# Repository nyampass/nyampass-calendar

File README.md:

# nyampass-calendar

A project to manage Calendar PCBs.

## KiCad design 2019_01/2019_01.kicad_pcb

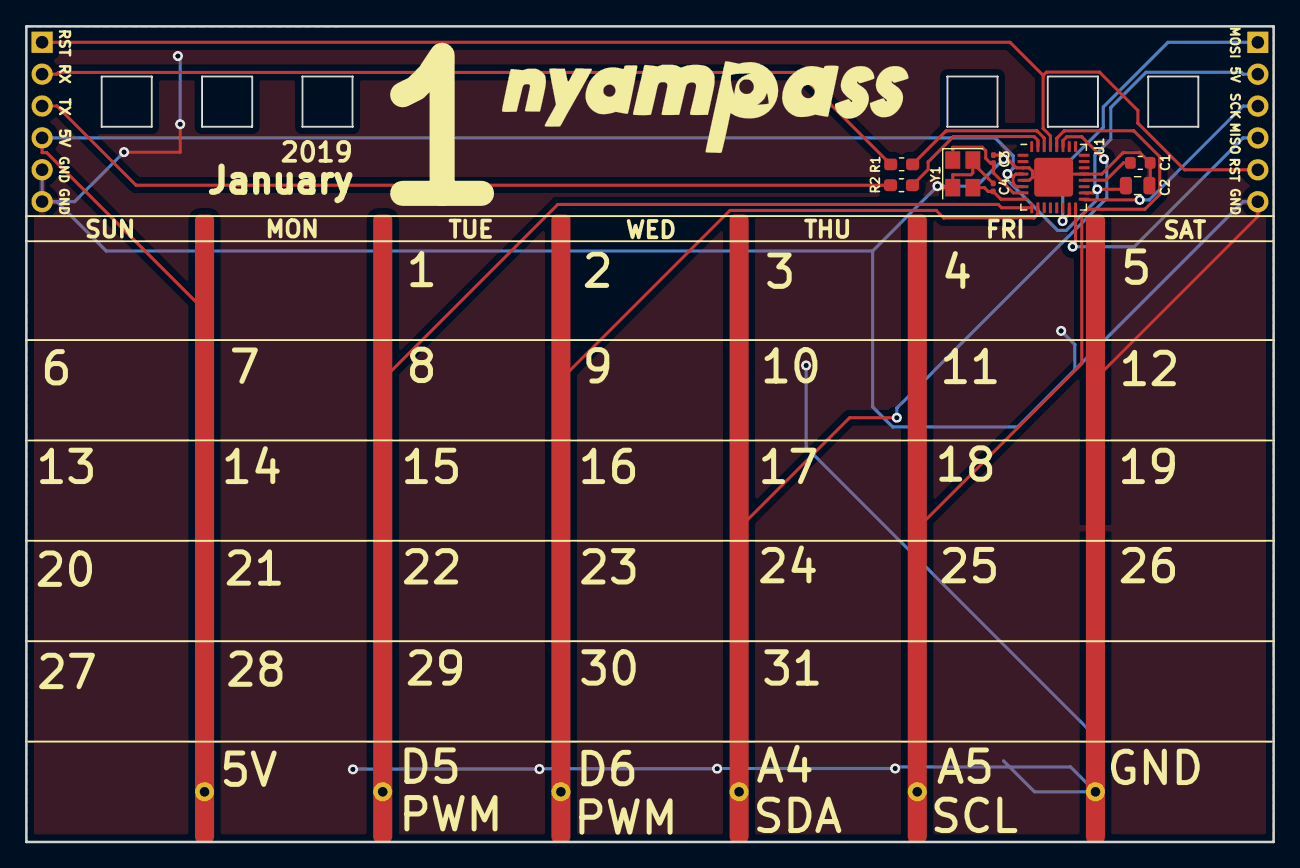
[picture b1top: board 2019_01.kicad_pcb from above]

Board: 2 copper layers, 99.4 x 65.0 mm, 18 parts (0 on the bottom side), 17 nets.

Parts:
C1: 0.1uf; C_0603_1608Metric
C2: 10uf; C_0805_2012Metric
C3, C4: 12pf; C_0201_0603Metric
J1: Write; PinHeader_1x06_P2.54mm_Vertical_without_silk
J2: ISP; PinHeader_1x06_P2.54mm_Vertical_without_silk
J3, J4, J5, J6, J7, J8: Line; calendar_vertical_line
R1, R2: 1k; R_0603_1608Metric_Pad1.05x0.95mm_HandSolder
REF1, REF2: calendar_hole
U1: ATmega328P-MU; QFN-32-1EP_5x5mm_P0.5mm_EP3.1x3.1mm
Y1: Crystal; Crystal_SMD_SeikoEpson_FA238-4Pin_3.2x2.5mm

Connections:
+5V: C2.1, J1.4, J2.2, J3.1, U1.4, U1.6, U1.18
A4-SDA: J6.1, U1.27
A5-SCL: J7.1, U1.28
D5: J4.1, U1.9
D6: J5.1, U1.10
GND: C1.1, C2.2, C3.2, C4.2, J1.5, J1.6, J2.6, J8.1, U1.3, U1.5, U1.21, U1.33, Y1.2, Y1.4
MISO: J2.4, U1.16
MOSI: J2.1, U1.15
unnamed: C1.2, U1.20
unnamed: C3.1, U1.7, Y1.1
unnamed: C4.1, U1.8, Y1.3
unnamed: R1.2, U1.30
unnamed: R2.2, U1.31
RST: J1.1, J2.5, U1.29
RX: J1.2, R1.1
SCK: J2.3, U1.17
TX: J1.3, R2.1

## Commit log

2018-12-10 Add logo to back side
2018-12-10 Export gerber files
2018-12-10 Add bom list
2018-12-11 Add header and urls for bom
2018-12-17 Create pcb directory
2018-12-18 Add atmega program
